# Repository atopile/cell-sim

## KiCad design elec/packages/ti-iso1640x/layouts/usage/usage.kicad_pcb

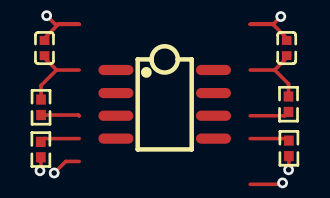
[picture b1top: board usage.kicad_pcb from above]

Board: 2 copper layers, 7 parts (0 on the bottom side), 6 nets.

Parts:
C1, C2: 100nF; C0402
R1, R2, R3, R4: 10kΩ; R0402
U1: SOIC-8_L5.0-W4.0-P1.27-LS6.0-BL

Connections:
SCL: R1.2, R2.2, U1.2, U1.4
SDA: R3.2, R4.2, U1.1, U1.8
hv: C1.1, R1.1, R3.1, U1.7
lv: C1.2, U1.6
power_rails[1]-hv: C2.1, R2.1, R4.1, U1.5
power_rails[1]-lv: C2.2, U1.3

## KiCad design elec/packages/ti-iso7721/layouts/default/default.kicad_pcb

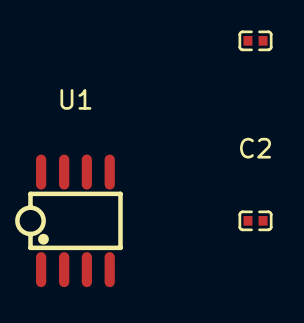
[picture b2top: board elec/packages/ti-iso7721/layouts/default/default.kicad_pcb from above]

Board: 2 copper layers, 3 parts (0 on the bottom side), 4 nets, no tracks yet.

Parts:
C1, C2: 100nF; C0402
U1: SOIC-8_L5.0-W4.0-P1.27-LS6.0-BL

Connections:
decap_card-power-hv: C2.1, U1.1
decap_card-power-lv: C2.2, U1.4
hv: C1.1, U1.8
lv: C1.2, U1.5

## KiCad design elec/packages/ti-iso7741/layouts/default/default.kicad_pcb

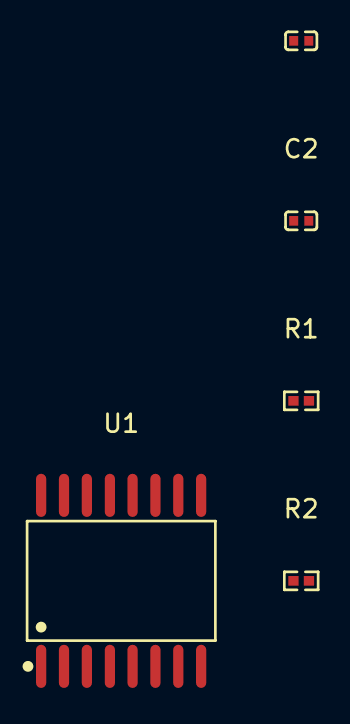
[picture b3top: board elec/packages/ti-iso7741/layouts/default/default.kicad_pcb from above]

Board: 2 copper layers, 5 parts (0 on the bottom side), 6 nets, no tracks yet.

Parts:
C1, C2: 100nF; C0402
R1, R2: 10kΩ; R0402
U1: SOIC-16_L10.3-W7.5-P1.27-LS10.3-BL

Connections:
7: R1.2, U1.7
10: R2.2, U1.10
decap_side2-power-hv: C2.1, R2.1, U1.16
decap_side2-power-lv: C2.2, U1.9, U1.15
hv: C1.1, R1.1, U1.1
lv: C1.2, U1.2, U1.8

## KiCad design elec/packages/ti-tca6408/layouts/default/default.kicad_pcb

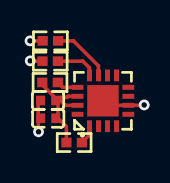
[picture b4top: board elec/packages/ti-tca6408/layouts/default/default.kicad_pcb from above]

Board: 2 copper layers, 7 parts (0 on the bottom side), 6 nets.

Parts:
C1, C2: 100nF; C0402
R1, R2, R3, R4: 4.7kΩ; R0402
U1: QFN-16_L3.0-W3.0-P0.50-BL-EP1.7

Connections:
SCL: R2.1, U1.12
SDA: R3.1, U1.13
hv: C1.1, C2.1, R1.1, R2.2, R3.2, R4.1, U1.14, U1.15
lv: C1.2, C2.2, U1.6, U1.16, U1.17
nINT: R4.2, U1.11
nRESET: R1.2, U1.1

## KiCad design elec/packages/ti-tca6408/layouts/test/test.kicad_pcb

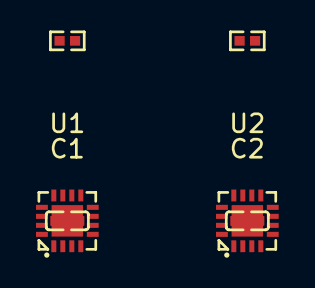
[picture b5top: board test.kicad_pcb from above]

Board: 2 copper layers, 6 parts (0 on the bottom side), 6 nets.

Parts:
C1, C2: 100nF ±10% 16V X7R; C0402
R1, R2: 10kΩ ±1% 62.5mW; R0402
U1, U2: QFN-16_L3.0-W3.0-P0.50-BL-EP1.7

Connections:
SCL: U1.12, U2.12
SDA: U1.13, U2.13
VCCI: C1.1, C2.1, R1.2, R2.2, U1.14, U1.15, U2.14, U2.15, U2.16
expanders[0]-RESET: R1.1, U1.1
expanders[1]-RESET: R2.1, U2.1
gnd: C1.2, C2.2, U1.6, U1.16, U1.17, U2.6, U2.17
